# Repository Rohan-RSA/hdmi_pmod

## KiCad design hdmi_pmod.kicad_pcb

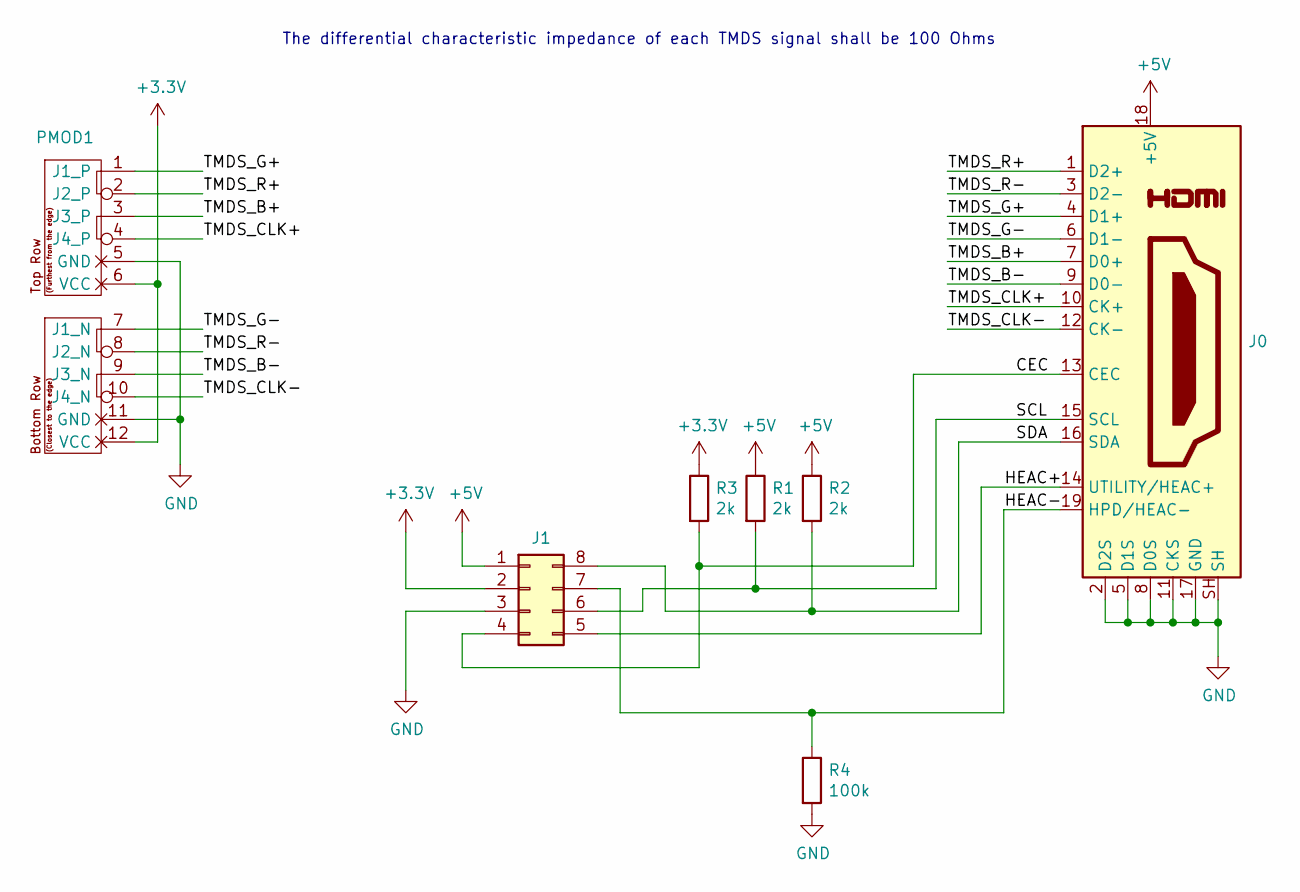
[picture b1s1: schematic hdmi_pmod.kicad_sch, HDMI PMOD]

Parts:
J0: HDMI_A_1.4; 10029449-111RLF
J1: Conn_02x04_Counter_Clockwise; PinHeader_2x04_P2.54mm_Vertical
PMOD1: PMOD_PMOD-Device-x2-Type-XHS-MODIFIED; pmod_pin_array_6x2_hs_modified
R1, R2, R3: 2k; R_0805_2012Metric
R4: 100k; R_0805_2012Metric

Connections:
+3.3V: J1.2, PMOD1.6 (VCC), PMOD1.12 (VCC), R3.1
+5V: J0.18 (+5V), J1.1, R1.1, R2.1
/CEC: J0.13 (CEC), J1.4, R3.2
/HEAC+: J0.14 (UTILITY/HEAC+), J1.5
/HEAC-: J0.19 (HPD/HEAC-), J1.7, R4.1
/SCL: J0.15 (SCL), J1.6, R1.2
/SDA: J0.16 (SDA), J1.8, R2.2
/TMDS_B+: J0.7 (D0+), PMOD1.3 (J3_P)
/TMDS_B-: J0.9 (D0-), PMOD1.9 (J3_N)
/TMDS_CLK+: J0.10 (CK+), PMOD1.4 (J4_P)
/TMDS_CLK-: J0.12 (CK-), PMOD1.10 (J4_N)
/TMDS_G+: J0.4 (D1+), PMOD1.1 (J1_P)
/TMDS_G-: J0.6 (D1-), PMOD1.7 (J1_N)
/TMDS_R+: J0.1 (D2+), PMOD1.2 (J2_P)
/TMDS_R-: J0.3 (D2-), PMOD1.8 (J2_N)
GND: J0.2 (D2S), J0.5 (D1S), J0.8 (D0S), J0.11 (CKS), J0.17 (GND), J0.SH, J1.3, PMOD1.5 (GND), PMOD1.11 (GND), R4.2

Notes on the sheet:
The differential characteristic impedance of each TMDS signal shall be 100 Ohms

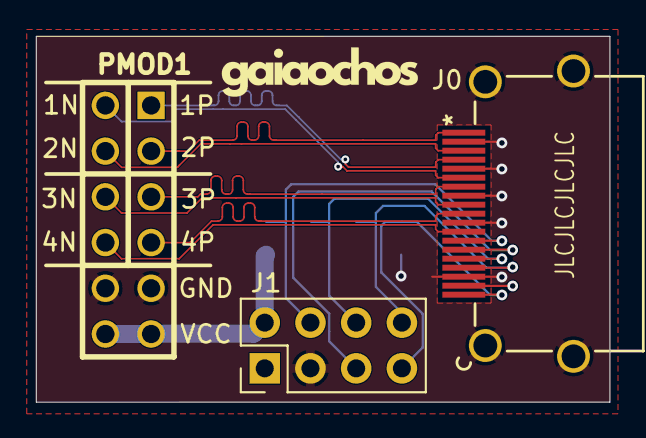
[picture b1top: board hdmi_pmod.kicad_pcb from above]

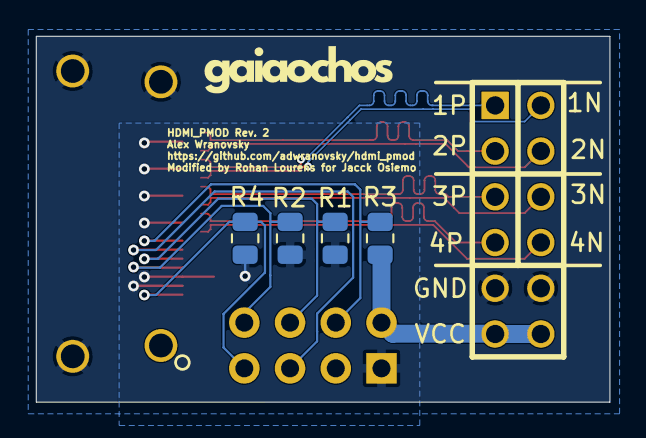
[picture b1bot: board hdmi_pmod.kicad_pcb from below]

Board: 4 copper layers, 31.9 x 20.3 mm, 7 parts (4 on the bottom side), 16 nets.

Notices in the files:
parts and their libraries:
Copyright 2016 Accelerated Designs. All rights reserved.
